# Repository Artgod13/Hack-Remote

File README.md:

# Hack-Remote
A cool remote that lets you control RF signals with a CC1101 module.
It has been specifically designed with customibilty in the code and ease of use in mind.
(Be careful to follow all radio laws in your area of jurisdiction)

 ---
 How this works is when you plug it into a power source to turn it on, you open up to a menu of different Mhz frequencies. At this menu you can scroll through different Mhz frequencies and click the rotary encoder switch to send out you're desired signal. I also added a signal called 676767 (Really funny I know). When you choose this signal it sends out the same message on 50 randomly chosen Mhz frequencies on at a time in quick succession to "test" RF signal receivers. I have made the code simple and easy to understand so that someone can go in and add their own desired Mhz frequencies and messages.
 
 ---
 I decided to make this, as I am constantly surrounded by RF receivers and transmitors. So why not build a simple device that is kinda like a flipper zero, and can manipulate/work with these RF signals. (Also flipper zeros are super expensive so if you want to make one but for like only RF here you go!)
 
 ---
 # Build Instructions:
Assembling the Hack Remote is very simple, all you need is a soldering iron, solder, 3d printed parts, PCB board, and all the parts in the BOM. First get the PCB board and place the compoments all facing up, and solder them onto their designated spots one by one. Next you want to flash the code onto the board, you do this by opening arduino IDE opening the code selecting the Xiao RP2040, and installing the Adafruit BusIO, AdafruitGFX Library, AdafruitSSD1306, RotaryEncoder, and SmartRC-CC1101-Driver-Lib Libraries. Then connnect you're board to the computer, and click upload on ArduinoIDE. After this get the Hack Remote bottom 3d printed part and put the assembled board onto it so that the Xiao usb-c end can be seen sticking out the power hole. Then screw the board on using 2 screws to make sure it stays in place. Finally put the Hack Remote Top on top of the bottom piece and use the rest of the screws to screw it in place. After all this work you should finally have a assembled Hack Remote ready to be used.

 ---
 # CAD MODEL:

These models were fully designed, and assembled in onshape.
https://cad.onshape.com/documents/6f64acb43278fcf02d95f203/w/43ea7b20cd107b410569e89b/e/a30772a52d9b3aa84b86adaa?renderMode=0&uiState=69fd384367af19aa08245193

---
# PCB:

These were fully made on KiCad

---

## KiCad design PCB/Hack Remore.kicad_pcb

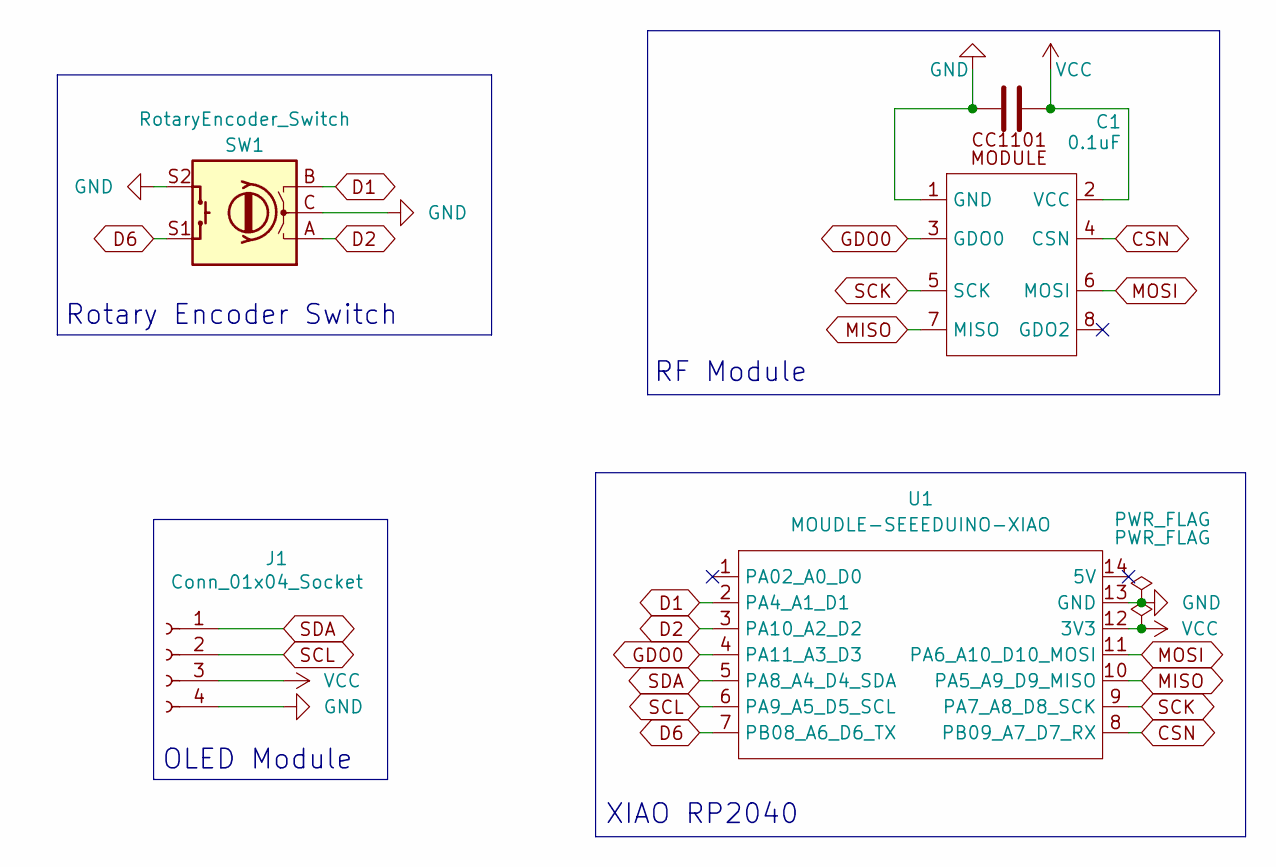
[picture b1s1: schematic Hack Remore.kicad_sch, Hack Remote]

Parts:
C1: 0.1uF; C_0805_2012Metric
J1: Conn_01x04_Socket; PinHeader_1x04_P2.54mm_Vertical
SW1: RotaryEncoder_Switch; RotaryEncoder_Alps_EC11E-Switch_Vertical_H20mm_MountingHoles
U1: MOUDLE-SEEEDUINO-XIAO; XIAO-Generic-Hybrid-14P-2.54-21X17.8MM
U3: PinSocket_2x04_P2.54mm_Vertical

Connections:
CSN: U1.8 (PB09_A7_D7_RX), U3.4 (CSN)
D1: SW1.B, U1.2 (PA4_A1_D1)
D2: SW1.A, U1.3 (PA10_A2_D2)
D6: SW1.S1, U1.7 (PB08_A6_D6_TX)
GDO0: U1.4 (PA11_A3_D3), U3.3 (GDO0)
GND: C1.2, J1.4, SW1.C, SW1.S2, U1.13 (GND), U3.1 (GND)
MISO: U1.10 (PA5_A9_D9_MISO), U3.7 (MISO)
MOSI: U1.11 (PA6_A10_D10_MOSI), U3.6 (MOSI)
SCK: U1.9 (PA7_A8_D8_SCK), U3.5 (SCK)
SCL: J1.2, U1.6 (PA9_A5_D5_SCL)
SDA: J1.1, U1.5 (PA8_A4_D4_SDA)
VCC: C1.1, J1.3, U1.12 (3V3), U3.2 (VCC)

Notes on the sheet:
RF Module
Rotary Encoder Switch
XIAO RP2040
OLED Module

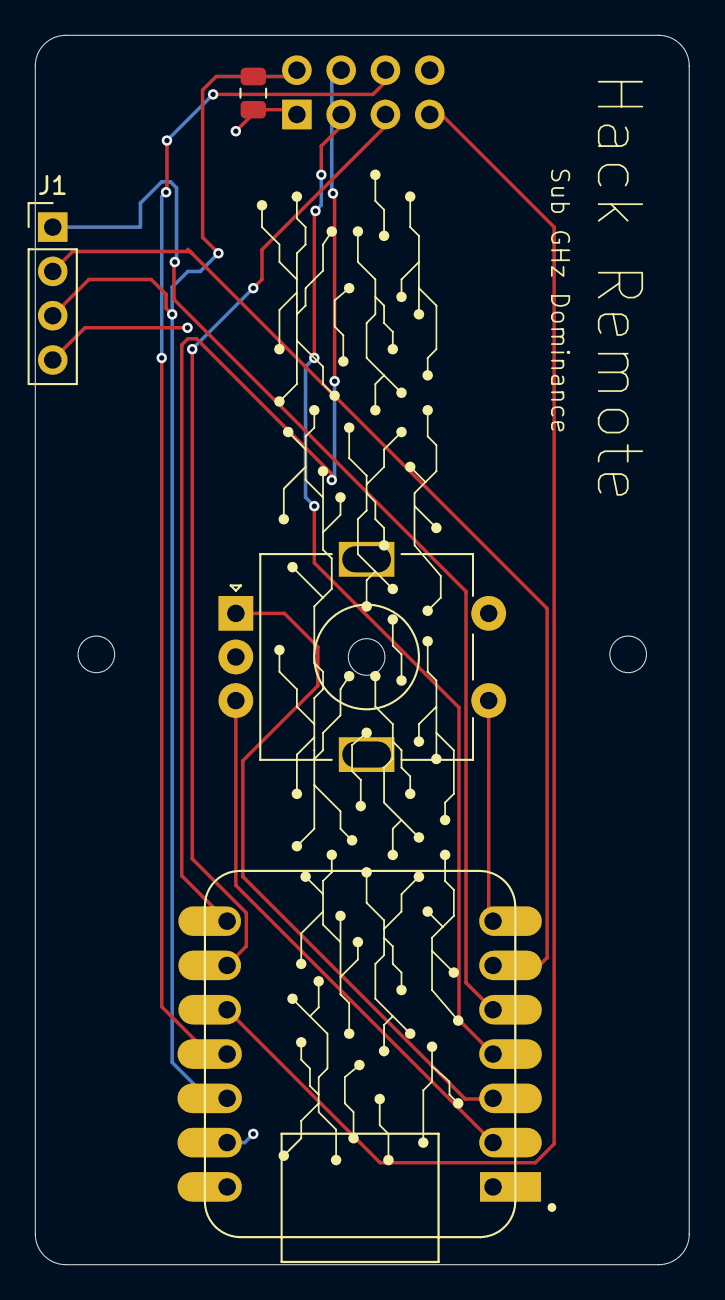
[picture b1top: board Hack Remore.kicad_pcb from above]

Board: 2 copper layers, 37.5 x 70.5 mm, 5 parts (1 on the bottom side), 12 nets.

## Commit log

2026-05-07 Create a
2026-05-08 Update README with image and functionality details
    Added an image and expanded the explanation of functionality.
2026-05-08 Add assembly instructions for Hack Remote
    Added assembly instructions for the Hack Remote, detailing the components needed and the steps to complete the assembly process.
2026-05-08 Add build instructions for Hack Remote assembly
    Added build instructions for assembling the Hack Remote, including required components and steps for flashing the code.
2026-05-08 Fix build instructions formatting and typos
    Corrected formatting and spelling errors in the README.
2026-05-08 Fix typos and enhance build instructions in README
    Corrected typos and improved clarity in build instructions.
2026-05-08 Update BOM with new items and URLs
2026-05-08 Update README with CAD model link
    Added a link to the CAD model documentation in the README.
2026-05-09 Update README with caution about radio laws
    Added a cautionary note about following radio laws.
